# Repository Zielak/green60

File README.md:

# green60

a backup of my failed attempt at designing a keyboard

maybe I'll get back at it at some point

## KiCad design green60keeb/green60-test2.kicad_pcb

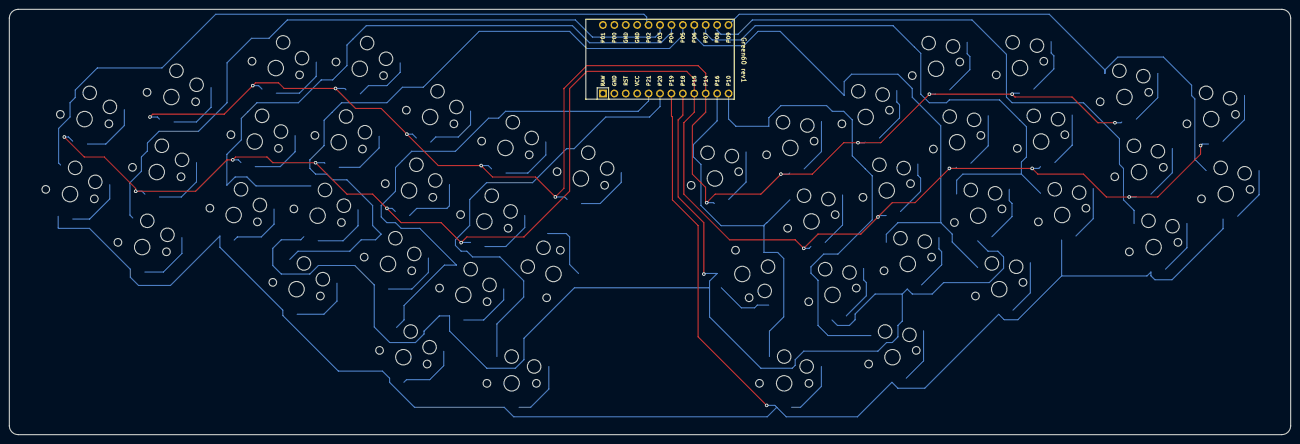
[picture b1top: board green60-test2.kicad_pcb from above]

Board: 2 copper layers, 285.0 x 94.6 mm, 45 parts (0 on the bottom side), 16 nets.

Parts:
MCU1: ProMicro
S1, S2, S3, S4, S5, S6, S7, S8, S9, S10, S11, S12, S13, S14, S15, S16, S17, S18, S19, S20, S21, S22, S23, S24, S25, S26, S27, S28, S29, S30, S31, S32, S33, S34, S35, S36, S37, S38, S39, S40, S41, S42, S43, S44: PG1350

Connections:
P2: MCU1.17, S1.1, S2.1, S5.1
P3: MCU1.18, S3.1, S4.1, S8.1
P4: MCU1.19, S6.1, S7.1, S10.1, S12.1
P5: MCU1.20, S9.1, S11.1, S13.1, S15.1
P6: MCU1.21, S31.1, S33.1, S35.1, S37.1
P7: MCU1.22, S28.1, S29.1, S32.1, S34.1
P8: MCU1.23, S25.1, S26.1, S30.1
P9: MCU1.24, S23.1, S24.1, S27.1
P10: MCU1.12, S36.1, S38.1, S40.1, S43.1
P14: MCU1.10, S5.3, S8.3, S12.3, S15.3, S18.3, S20.3, S27.3, S30.3, S34.3, S37.3, S40.3, S42.3
P15: MCU1.9, S2.3, S4.3, S7.3, S11.3, S14.3, S17.3, S24.3, S26.3, S29.3, S33.3, S36.3, S39.3
P16: MCU1.11, S39.1, S41.1, S42.1, S44.1
P18: MCU1.8, S10.3, S13.3, S16.3, S19.3, S32.3, S35.3, S38.3, S41.3
P19: MCU1.7, S1.3, S3.3, S6.3, S9.3, S21.3, S22.3, S23.3, S25.3, S28.3, S31.3, S43.3, S44.3
P20: MCU1.6, S17.1, S19.1, S20.1, S22.1
P21: MCU1.5, S14.1, S16.1, S18.1, S21.1

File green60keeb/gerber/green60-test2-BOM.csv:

"Id";"Oznaczenie";"Pakiet";"Ilość";"Oznaczenie";"Dostawca i numer artykułu";
1;"S1,S2,S3,S4,S5,S6,S7,S8,S9,S10,S11,S12,S13,S14,S15,S16,S17,S18,S19,S20,S21,S22,S23,S24,S25,S26,S27,S28,S29,S30,S31,S32,S33,S34,S35,S36,S37,S38,S39,S40,S41,S42,S43,S44";"PG1350";44;"";;;
2;"MCU1";"ProMicro";1;"";;;

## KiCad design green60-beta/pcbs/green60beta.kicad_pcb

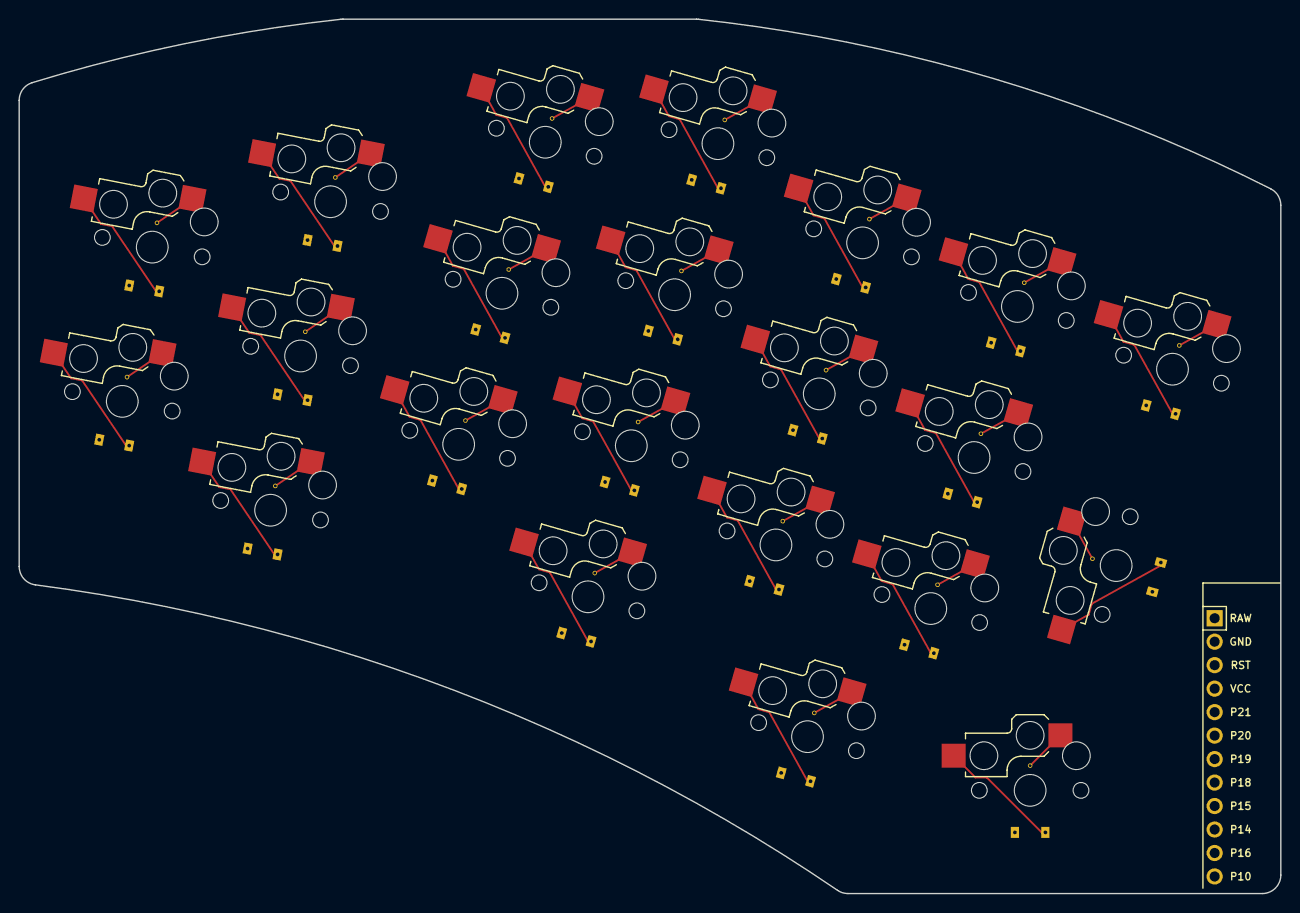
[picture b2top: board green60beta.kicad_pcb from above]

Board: 2 copper layers, 136.5 x 94.6 mm, 23 parts (0 on the bottom side), 32 nets, no tracks yet.

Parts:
MCU1: ProMicro
S1, S2, S3, S4, S5, S6, S7, S8, S9, S10, S11, S12, S13, S14, S15, S16, S17, S18, S19, S20, S21, S22: PG1350

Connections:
P2: MCU1.3, S1.1, S2.1, S5.1
P3: MCU1.4, S3.1, S4.1, S8.1
P4: MCU1.5, S6.1, S7.1, S10.1, S12.1
P5: MCU1.6, S9.1, S11.1, S13.1, S15.1
P14: S5.3, S8.3, S12.3, S15.3, S18.3, S20.3
P15: S2.3, S4.3, S7.3, S11.3, S14.3, S17.3
P18: S10.3, S13.3, S16.3, S19.3
P19: S1.3, S3.3, S6.3, S9.3, S21.3, S22.3
P20: S17.1, S19.1, S20.1, S22.1
P21: S14.1, S16.1, S18.1, S21.1
S1_D: S1.2, S1.2D
S2_D: S2.2, S2.2D
S3_D: S3.2, S3.2D
S4_D: S4.2, S4.2D
S5_D: S5.2, S5.2D
S6_D: S6.2, S6.2D
S7_D: S7.2, S7.2D
S8_D: S8.2, S8.2D
S9_D: S9.2, S9.2D
S10_D: S10.2, S10.2D
S11_D: S11.2, S11.2D
S12_D: S12.2, S12.2D
S13_D: S13.2, S13.2D
S14_D: S14.2, S14.2D
S15_D: S15.2, S15.2D
S16_D: S16.2, S16.2D
S17_D: S17.2, S17.2D
S18_D: S18.2, S18.2D
S19_D: S19.2, S19.2D
S20_D: S20.2, S20.2D
S21_D: S21.2, S21.2D
S22_D: S22.2, S22.2D

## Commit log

2023-02-28 init
